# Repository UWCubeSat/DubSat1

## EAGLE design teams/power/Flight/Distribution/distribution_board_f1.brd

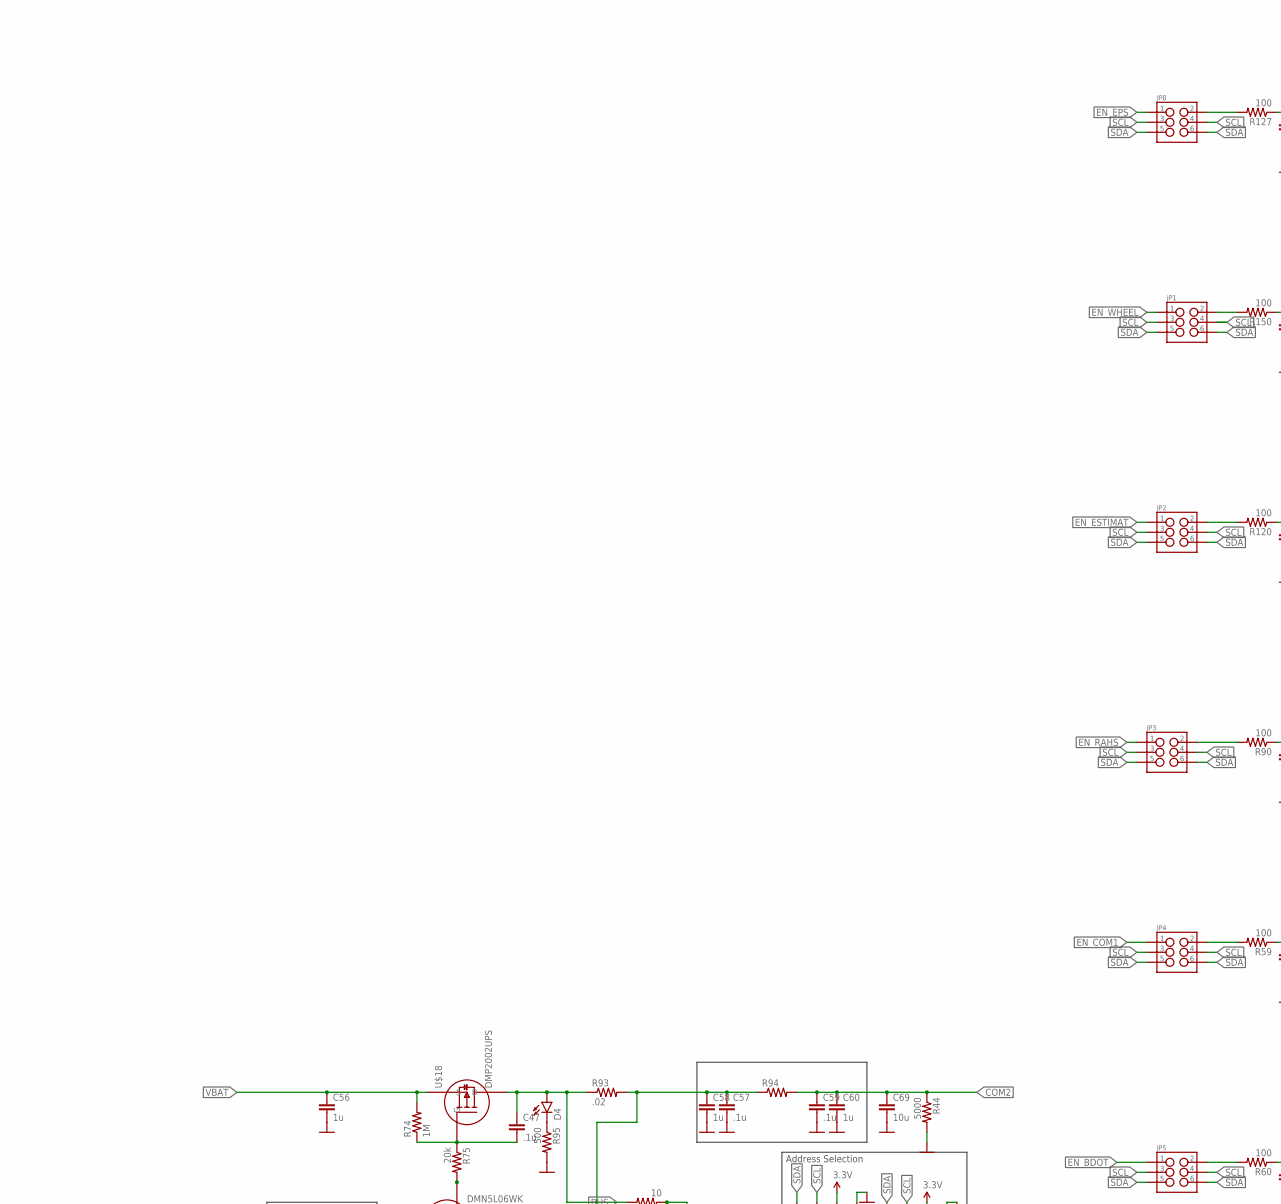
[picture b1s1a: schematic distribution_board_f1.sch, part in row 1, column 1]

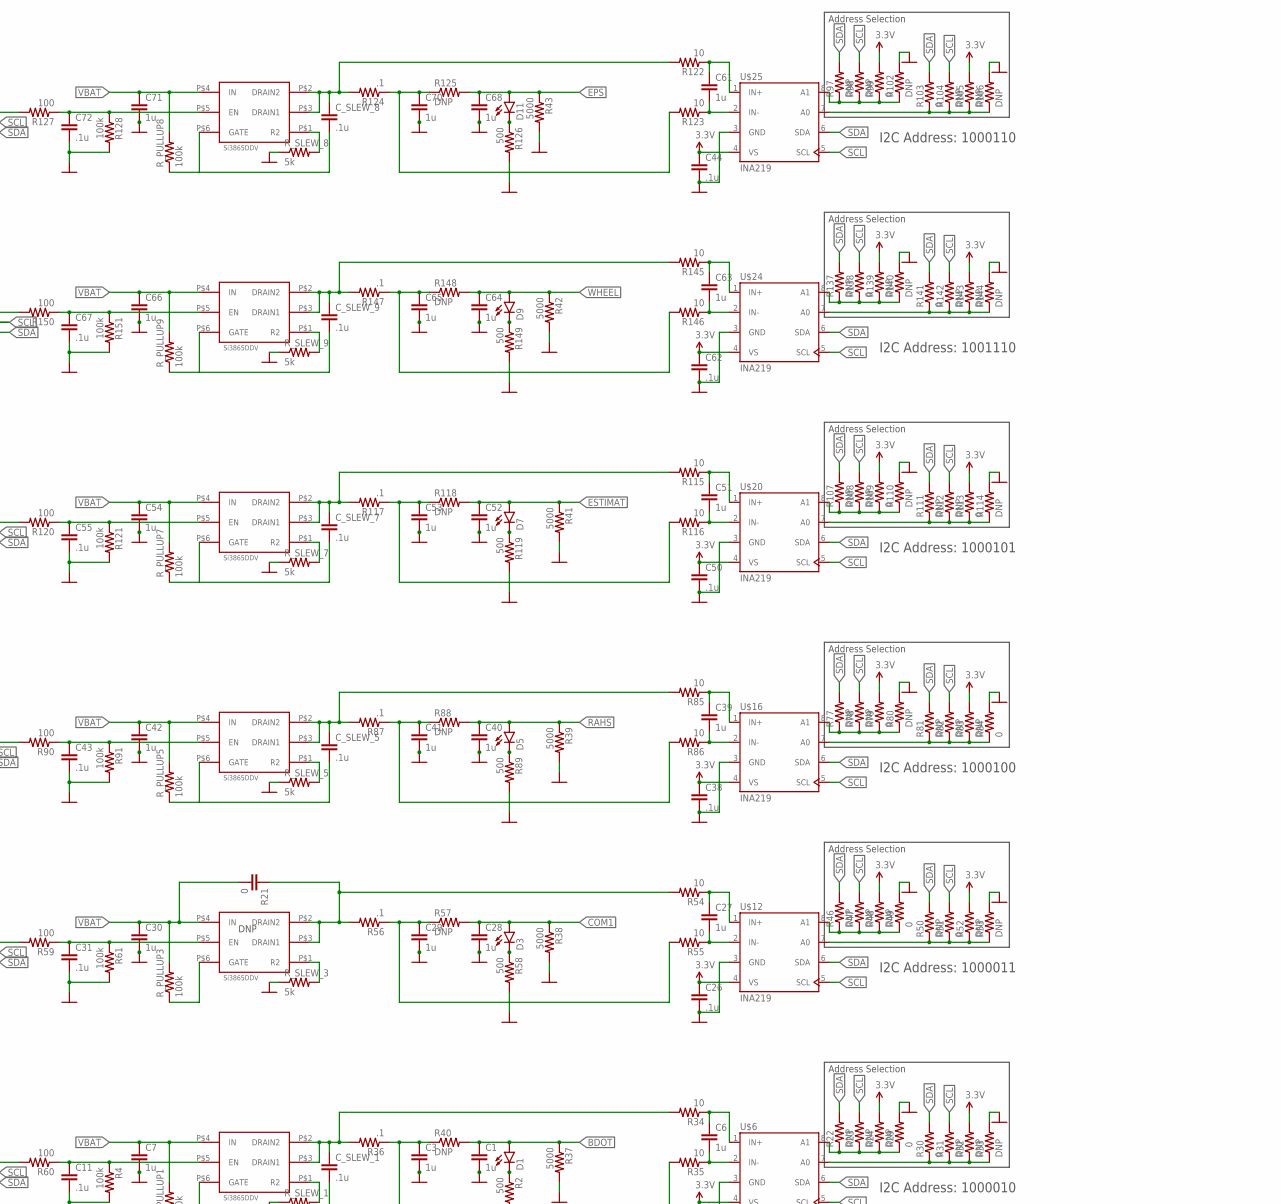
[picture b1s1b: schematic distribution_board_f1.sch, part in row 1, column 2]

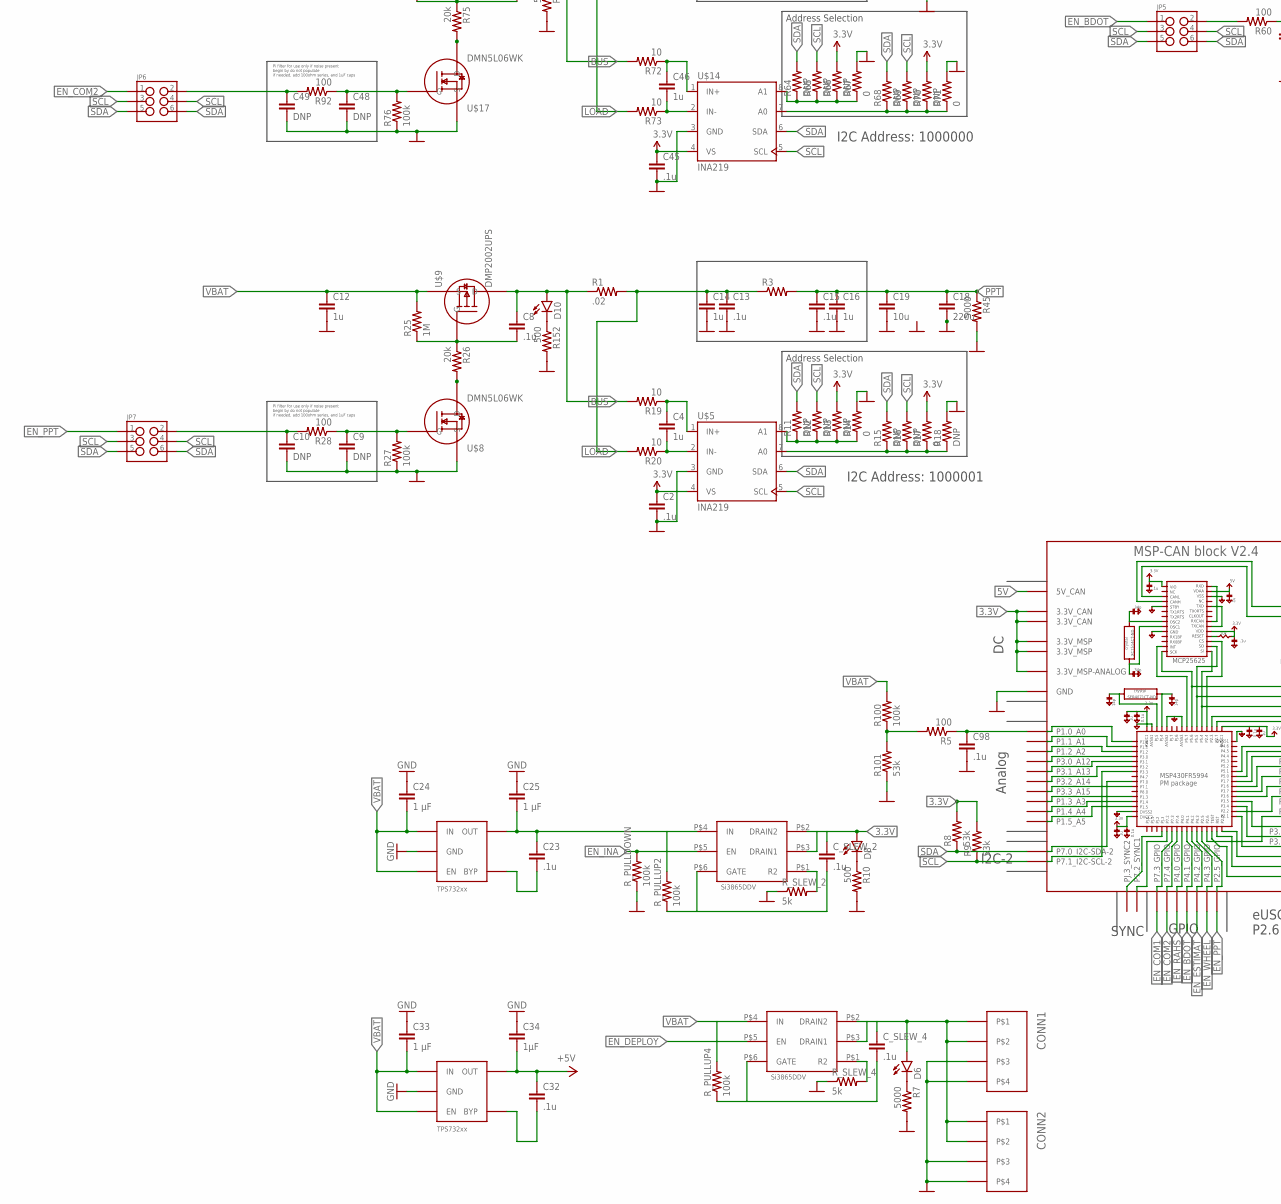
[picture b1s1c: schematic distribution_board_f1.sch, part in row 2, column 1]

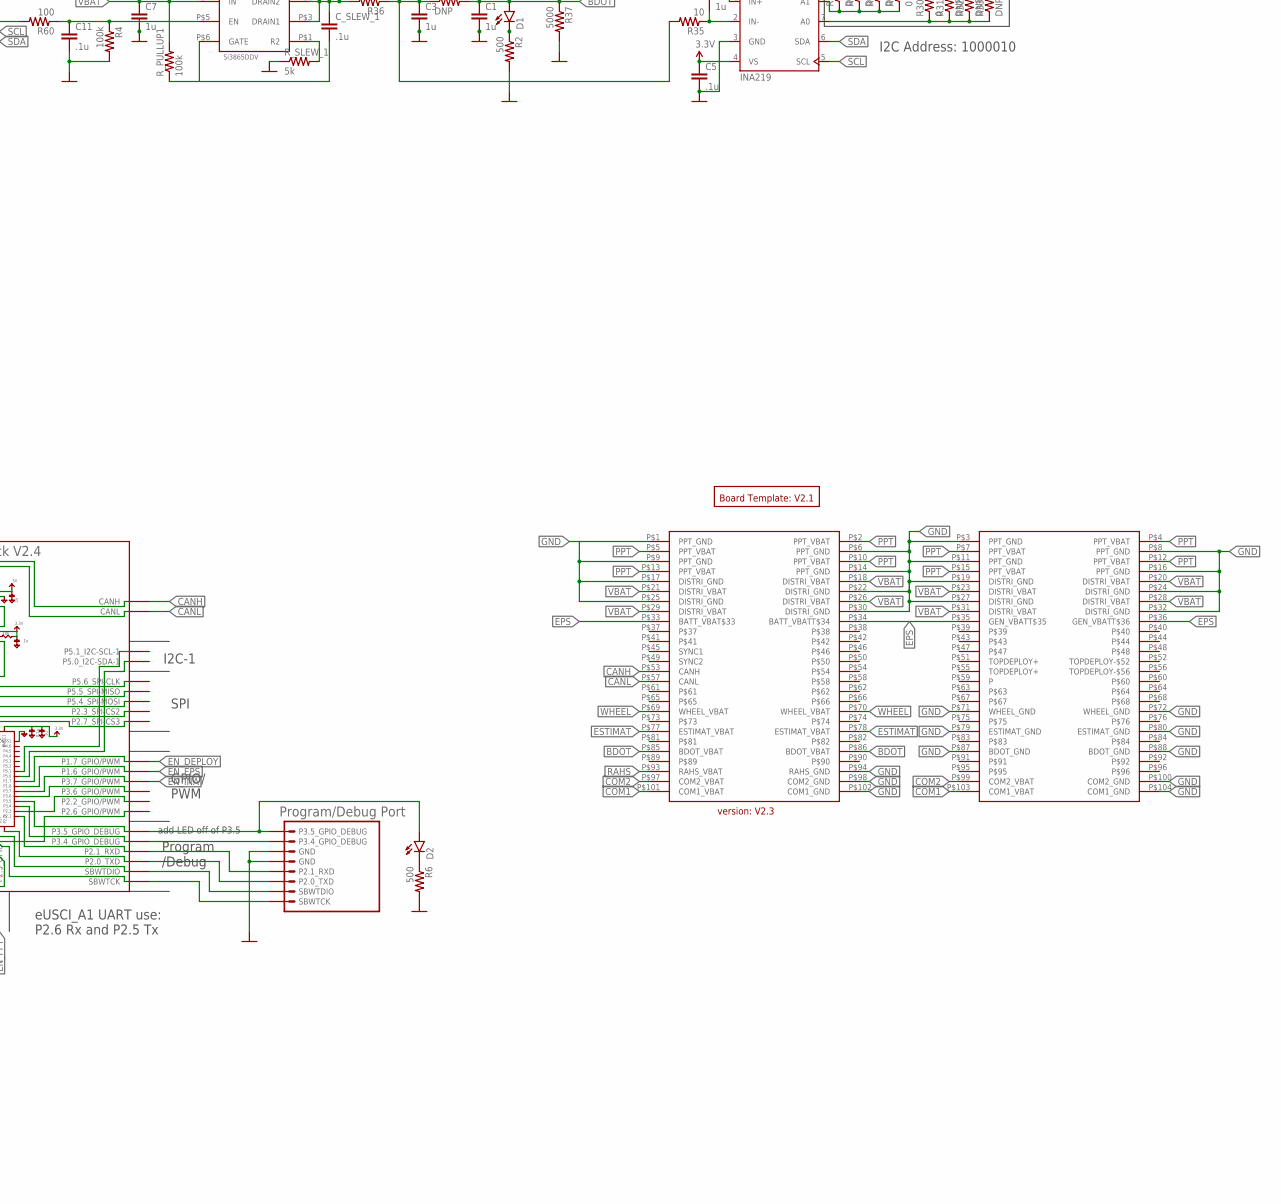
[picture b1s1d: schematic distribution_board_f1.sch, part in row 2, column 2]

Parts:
BLK1: MSP-CAN_BLOCK
C1, C3, C4, C6, C7, C12, C14, C16, C27, C28, C29, C30, C39, C40, C41, C42, C46, C51, C52, C53, C54, C56, C58, C60, C61, C63, C64, C65, C66, C68, C70, C71: 1u; 0805
C2, C5, C8, C11, C13, C15, C23, C26, C31, C32, C38, C43, C44, C45, C47, C50, C55, C57, C59, C62, C67, C72, C98: .1u; 0805
C9, C10, C48, C49: DNP; 0805
C18: 220u; 2917
C19, C69: 10u; 1210
C24, C25, C33: 1 μF; 0805
C34: 1μF; 0805
CONN1, CONN2: PICOLOCK_4-LEGACY
C_SLEW_1, C_SLEW_2, C_SLEW_4, C_SLEW_5, C_SLEW_7, C_SLEW_8, C_SLEW_9: .1u; 0805
D1, D2, D3, D4, D5, D6, D7, D8, D9, D10, D11: LED; LED-1206
JP1, JP2, JP3, JP4, JP5, JP6, JP7, JP8: M03X2NO_SILK; 2X3-NS
R1, R93: .02; R2010
R2, R6, R10, R58, R89, R95, R119, R126, R149, R152: 500; 0805
R3, R94: RESISTOR1206; 1206
R4, R27, R61, R76, R91, R100, R121, R128, R151: 100k; 0805
R5, R28, R59, R60, R90, R92, R120, R127, R150: 100; 0805
R7, R37, R38, R39, R41, R42, R43, R44, R45: 5000; 0805
R8, R9, R101: 53k; 0805
R11, R12, R13, R15, R16, R18, R22, R23, R24, R31, R32, R33, R40, R46, R47, R48, R50, R52, R53, R57, R64, R65, R66, R68, R69, R70, R77, R78, R80, R81, R82, R83, R88, R97, R98, R102, R104, R105, R106, R107, R108, R110, R111, R112, R114, R118, R125, R137, R139, R140, R142, R143, R144, R148: DNP; 0805
R14, R17, R21, R29, R30, R49, R51, R67, R71, R79, R84, R99, R103, R109, R113, R138, R141: 0; 0805
R19, R20, R34, R35, R54, R55, R72, R73, R85, R86, R115, R116, R122, R123, R145, R146: 10; 0805
R25, R74: 1M; 0805
R26, R75: 20k; 0805
R36, R56, R87, R117, R124, R147: .1; R2010
R_PULLDOWN: 100k; 0805
R_PULLUP1, R_PULLUP2, R_PULLUP3, R_PULLUP4, R_PULLUP5, R_PULLUP7, R_PULLUP8, R_PULLUP9: 100k; 0805
R_SLEW_1, R_SLEW_2, R_SLEW_3, R_SLEW_4, R_SLEW_5, R_SLEW_7, R_SLEW_8, R_SLEW_9: 5k; 0805
U2, U3: TPS732XX; SOT-23-5
U$1: PROGRAM/DEBUG_PORT; 1X08_CONNECTOR
U$2: PC104_CONNECTOR
U$3: BOARD_TEMPLATE1; BOARD_TEMPLATE
U$5, U$6, U$12, U$14, U$16, U$20, U$24, U$25: INA219; SOT-23-8
U$7, U$10, U$11, U$13, U$15, U$19, U$22, U$23: SI3865DDV; TSOP-6
U$8, U$17: DMN5L06WK; SOT-323
U$9, U$18: DMP2002UPS; POWERDI5060-8

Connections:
3.3V: BLK1.3.3V@CAN1 (3.3V_CAN), BLK1.3.3V@CAN2 (3.3V_CAN), BLK1.3.3V@MSP1 (3.3V_MSP), BLK1.3.3V@MSP2 (3.3V_MSP), BLK1.3.3V_ANALOG@MSP2 (3.3V_MSP-ANALOG), C2.1, C5.1, C23.1, C25.2, C26.1, C38.1, C44.1, C45.1, C50.1, C62.1, C_SLEW_2.1, D8.A, R8.2, R9.2, R13.2, R17.2, R24.2, R32.2, R48.2, R52.2, R66.2, R70.2, R79.2, R83.2, R99.2, R105.2, R109.2, R113.2, R139.2, R143.2, R_PULLUP2.2, U2.P$5 (OUT), U$5.4 (VS), U$6.4 (VS), U$7.P$2 (DRAIN2), U$7.P$3 (DRAIN1), U$7.P$4 (IN), U$12.4 (VS), U$14.4 (VS), U$16.4 (VS), U$20.4 (VS), U$24.4 (VS), U$25.4 (VS)
5V: BLK1.5V (5V_CAN), C32.1, C34.2, U3.P$5 (OUT)
BDOT: C1.1, D1.A, R37.1, R40.2, U$2.P$85 (BDOT_VBAT), U$2.P$86 (BDOT_VBAT)
BUS: C8.1, C47.1, D4.A, D10.A, R1.1, R19.2, R72.2, R93.1, U$9.D1 (D), U$9.D2 (D), U$9.D3 (D), U$9.D4 (D), U$9.D5 (D), U$18.D1 (D), U$18.D2 (D), U$18.D3 (D), U$18.D4 (D), U$18.D5 (D)
CANH: BLK1.CANH, U$2.P$53 (CANH)
CANL: BLK1.CANL, U$2.P$57 (CANL)
COM1: C28.1, D3.A, R38.1, R57.2, U$2.P$101 (COM1_VBAT), U$2.P$103 (COM1_VBAT)
COM2: C59.1, C60.1, C69.1, R44.1, R94.2, U$2.P$97 (COM2_VBAT), U$2.P$99 (COM2_VBAT)
DEPLOY: CONN1.P$1, CONN1.P$2, CONN2.P$1, CONN2.P$2, C_SLEW_4.1, D6.A, U$13.P$2 (DRAIN2), U$13.P$3 (DRAIN1)
EN_BDOT: BLK1.P4.1_GPIO, JP5.1, JP5.2, R60.2
EN_COM1: BLK1.P7.3_GPIO, JP4.1, JP4.2, R59.2
EN_COM2: BLK1.P7.4_GPIO, C49.1, JP6.1, JP6.2, R92.2
EN_DEPLOY: BLK1.P1.7_GPIO/PWM, U$13.P$5 (EN)
EN_EPS: BLK1.P1.6_GPIO/PWM, JP8.1, JP8.2, R127.2
EN_ESTIMAT: BLK1.P4.2_GPIO, JP2.1, JP2.2, R120.2
EN_INA: BLK1.P3.7_GPIO/PWM, R_PULLDOWN.2, U$7.P$5 (EN)
EN_PPT: BLK1.P2.5_GPIO, C10.1, JP7.1, JP7.2, R28.2
EN_RAHS: BLK1.P4.0_GPIO, JP3.1, JP3.2, R90.2
EN_WHEEL: BLK1.P4.3_GPIO, JP1.1, JP1.2, R150.2
EPS: C68.1, D11.A, R43.1, R125.2, U$2.P$33 (BATT_VBAT$33), U$2.P$34 (BATT_VBATT$34), U$2.P$35 (GEN_VBATT$35), U$2.P$36 (GEN_VBATT$36)
ESTIMAT: C52.1, D7.A, R41.1, R118.2, U$2.P$77 (ESTIMAT_VBAT), U$2.P$78 (ESTIMAT_VBAT)
GND: BLK1.GND@1 (GND), BLK1.GND@2 (GND), BLK1.GND@3 (GND), BLK1.GND@4 (GND), BLK1.GND@5 (GND), BLK1.GND@7 (GND), BLK1.GND@8 (GND), BLK1.GND@9 (GND), BLK1.GND@10 (GND), BLK1.GND@11 (GND), BLK1.GND@12 (GND), BLK1.GND@13 (GND), BLK1.GND@14 (GND), BLK1.GND@15 (GND), BLK1.GND@16 (GND), BLK1.GND@17 (GND), BLK1.GND@26 (GND), C1.2, C2.2, C3.2, C5.2, C7.2, C9.2, C10.2, C11.2, C12.2, C13.2, C14.2, C15.2, C16.2, C18.2, C19.2, C24.1, C25.1, C26.2, C28.2, C29.2, C30.2, C31.2, C33.1, C34.1, C38.2, C40.2, C41.2, C42.2, C43.2, C44.2, C45.2, C48.2, C49.2, C50.2, C52.2, C53.2, C54.2, C55.2, C56.2, C57.2, C58.2, C59.2, C60.2, C62.2, C64.2, C65.2, C66.2, C67.2, C68.2, C69.2, C70.2, C71.2, C72.2, C98.2, CONN1.P$3, CONN1.P$4, CONN2.P$3, CONN2.P$4, R2.2, R4.2, R6.2, R7.2, R10.2, R14.2, R18.2, R27.1, R29.2, R33.2, R37.2, R38.2, R39.2, R41.2, R42.2, R43.2, R44.2, R45.2, R49.2, R53.2, R58.2, R61.2, R67.2, R71.2, R76.1, R80.2, R84.2, R89.2, R91.2, R95.2, R101.1, R102.2, R106.2, R110.2, R114.2, R119.2, R121.2, R126.2, R128.2, R140.2, R144.2, R149.2, R151.2, R152.2, R_PULLDOWN.1, R_SLEW_1.1, R_SLEW_2.1, R_SLEW_3.1, R_SLEW_4.1, R_SLEW_5.1, R_SLEW_7.1, R_SLEW_8.1, R_SLEW_9.1, U2.P$2 (GND), U3.P$2 (GND), U$1.5 (GND), U$1.6 (GND), U$2.P$1 (PPT_GND), U$2.P$3 (PPT_GND), U$2.P$6 (PPT_GND), U$2.P$8 (PPT_GND), U$2.P$9 (PPT_GND), U$2.P$11 (PPT_GND), U$2.P$14 (PPT_GND), U$2.P$16 (PPT_GND), U$2.P$17 (DISTRI_GND), U$2.P$19 (DISTRI_GND), U$2.P$22 (DISTRI_GND), U$2.P$24 (DISTRI_GND), U$2.P$27 (DISTRI_GND), U$2.P$30 (DISTRI_GND), U$2.P$32 (DISTRI_GND), U$2.P$71 (WHEEL_GND), U$2.P$72 (WHEEL_GND), U$2.P$79 (ESTIMAT_GND), U$2.P$80 (ESTIMAT_GND), U$2.P$87 (BDOT_GND), U$2.P$88 (BDOT_GND), U$2.P$94 (RAHS_GND), U$2.P$98 (COM2_GND), U$2.P$100 (COM2_GND), U$2.P$102 (COM1_GND), U$2.P$104 (COM1_GND), U$5.3 (GND), U$6.3 (GND), U$8.2 (S), U$12.3 (GND), U$14.3 (GND), U$16.3 (GND), U$17.2 (S), U$20.3 (GND), U$24.3 (GND), U$25.3 (GND)
INA219_A0_1: R15.1, R16.1, R17.1, R18.1, U$5.7 (A0)
INA219_A0_2: R30.1, R31.1, R32.1, R33.1, U$6.7 (A0)
INA219_A0_4: R50.1, R51.1, R52.1, R53.1, U$12.7 (A0)
INA219_A0_5: R68.1, R69.1, R70.1, R71.1, U$14.7 (A0)
INA219_A0_6: R81.1, R82.1, R83.1, R84.1, U$16.7 (A0)
INA219_A0_7: R103.1, R104.1, R105.1, R106.1, U$25.7 (A0)
INA219_A0_8: R111.1, R112.1, R113.1, R114.1, U$20.7 (A0)
INA219_A0_10: R141.1, R142.1, R143.1, R144.1, U$24.7 (A0)
INA219_A1_1: R11.1, R12.1, R13.1, R14.1, U$5.8 (A1)
INA219_A1_2: R22.1, R23.1, R24.1, R29.1, U$6.8 (A1)
INA219_A1_4: R46.1, R47.1, R48.1, R49.1, U$12.8 (A1)
INA219_A1_5: R64.1, R65.1, R66.1, R67.1, U$14.8 (A1)
INA219_A1_6: R77.1, R78.1, R79.1, R80.1, U$16.8 (A1)
INA219_A1_7: R97.1, R98.1, R99.1, R102.1, U$25.8 (A1)
INA219_A1_8: R107.1, R108.1, R109.1, R110.1, U$20.8 (A1)
INA219_A1_10: R137.1, R138.1, R139.1, R140.1, U$24.8 (A1)
INA219_IN+_1: C4.1, R19.1, U$5.1 (IN+)
INA219_IN+_2: C6.1, R34.1, U$6.1 (IN+)
INA219_IN+_4: C27.1, R54.1, U$12.1 (IN+)
INA219_IN+_5: C46.1, R72.1, U$14.1 (IN+)
INA219_IN+_6: C39.1, R85.1, U$16.1 (IN+)
INA219_IN+_7: C61.1, R122.1, U$25.1 (IN+)
INA219_IN+_8: C51.1, R115.1, U$20.1 (IN+)
INA219_IN+_10: C63.1, R145.1, U$24.1 (IN+)
INA219_IN-_1: C4.2, R20.1, U$5.2 (IN-)
INA219_IN-_2: C6.2, R35.1, U$6.2 (IN-)
INA219_IN-_4: C27.2, R55.1, U$12.2 (IN-)
INA219_IN-_5: C46.2, R73.1, U$14.2 (IN-)
INA219_IN-_6: C39.2, R86.1, U$16.2 (IN-)
INA219_IN-_7: C61.2, R123.1, U$25.2 (IN-)
INA219_IN-_8: C51.2, R116.1, U$20.2 (IN-)
INA219_IN-_10: C63.2, R146.1, U$24.2 (IN-)
LDO_3V3_BYP2: C23.2, U2.P$4 (BYP)
LDO_5V_BYP2: C32.2, U3.P$4 (BYP)
LOAD: C13.1, C14.1, C57.1, C58.1, R1.2, R3.1, R20.2, R73.2, R93.2, R94.1
unnamed: C8.2, R25.1, R26.1, U$9.G
unnamed: C9.1, R27.2, R28.1, U$8.1 (G)
unnamed: D1.C, R2.1
unnamed: C11.1, R4.1, R60.1, U$11.P$5 (EN)
unnamed: R5.2, R100.1, R101.2
unnamed: R26.2, U$8.3 (D)
unnamed: BLK1.P1.0_A0, C98.1, R5.1
unnamed: R_SLEW_2.2, U$7.P$1 (R2)
unnamed: R_SLEW_1.2, U$11.P$1 (R2)
unnamed: C_SLEW_1.2, R_PULLUP1.1, U$11.P$6 (GATE)
unnamed: C_SLEW_2.2, R_PULLUP2.1, U$7.P$6 (GATE)
unnamed: R_SLEW_3.2, U$10.P$1 (R2)
unnamed: R_PULLUP3.1, U$10.P$6 (GATE)
unnamed: D3.C, R58.1
unnamed: C31.1, R59.1, R61.1, U$10.P$5 (EN)
unnamed: C47.2, R74.1, R75.1, U$18.G
unnamed: C48.1, R76.2, R92.1, U$17.1 (G)
unnamed: R75.2, U$17.3 (D)
unnamed: D4.C, R95.1
unnamed: R_SLEW_5.2, U$15.P$1 (R2)
unnamed: C_SLEW_5.2, R_PULLUP5.1, U$15.P$6 (GATE)
unnamed: D5.C, R89.1
unnamed: C43.1, R90.1, R91.1, U$15.P$5 (EN)
unnamed: BLK1.P3.5_GPIO_DEBUG, D2.A, U$1.8 (P3.5_GPIO_DEBUG)
unnamed: BLK1.P3.4_GPIO_DEBUG, U$1.7 (P3.4_GPIO_DEBUG)
unnamed: BLK1.P2.1_RXD, U$1.4 (P2.1_RXD)
unnamed: BLK1.P2.0_TXD, U$1.3 (P2.0_TXD)
unnamed: R_SLEW_7.2, U$19.P$1 (R2)
unnamed: C_SLEW_7.2, R_PULLUP7.1, U$19.P$6 (GATE)
unnamed: D7.C, R119.1
unnamed: C55.1, R120.1, R121.1, U$19.P$5 (EN)
unnamed: BLK1.SBWTDIO, U$1.2 (SBWTDIO)
unnamed: BLK1.SBWTCK, U$1.SBWTCK
unnamed: R_SLEW_4.2, U$13.P$1 (R2)
unnamed: C_SLEW_4.2, R_PULLUP4.1, U$13.P$6 (GATE)
unnamed: R_SLEW_9.2, U$23.P$1 (R2)
unnamed: C_SLEW_9.2, R_PULLUP9.1, U$23.P$6 (GATE)
unnamed: D9.C, R149.1
unnamed: C67.1, R150.1, R151.1, U$23.P$5 (EN)
unnamed: D10.C, R152.1
unnamed: D2.C, R6.1
unnamed: D8.C, R10.1
unnamed: D6.C, R7.1
unnamed: R_SLEW_8.2, U$22.P$1 (R2)
unnamed: C_SLEW_8.2, R_PULLUP8.1, U$22.P$6 (GATE)
unnamed: D11.C, R126.1
unnamed: C72.1, R127.1, R128.1, U$22.P$5 (EN)
OUTPUT1: C3.1, R35.2, R36.1, R40.1
OUTPUT3: C29.1, R55.2, R56.1, R57.1
OUTPUT4: C70.1, R123.2, R124.1, R125.1
OUTPUT5: C41.1, R86.2, R87.1, R88.1
OUTPUT7: C53.1, R116.2, R117.1, R118.1
OUTPUT9: C65.1, R146.2, R147.1, R148.1
OUT_1: C_SLEW_1.1, R34.2, R36.2, U$11.P$2 (DRAIN2), U$11.P$3 (DRAIN1)
OUT_3: R21.1, R54.2, R56.2, U$10.P$2 (DRAIN2), U$10.P$3 (DRAIN1)
OUT_4: C_SLEW_8.1, R122.2, R124.2, U$22.P$2 (DRAIN2), U$22.P$3 (DRAIN1)
OUT_5: C_SLEW_5.1, R85.2, R87.2, U$15.P$2 (DRAIN2), U$15.P$3 (DRAIN1)
OUT_7: C_SLEW_7.1, R115.2, R117.2, U$19.P$2 (DRAIN2), U$19.P$3 (DRAIN1)
OUT_9: C_SLEW_9.1, R145.2, R147.2, U$23.P$2 (DRAIN2), U$23.P$3 (DRAIN1)
PPT: C15.1, C16.1, C18.1, C19.1, R3.2, R45.1, U$2.P$2 (PPT_VBAT), U$2.P$4 (PPT_VBAT), U$2.P$5 (PPT_VBAT), U$2.P$7 (PPT_VBAT), U$2.P$10 (PPT_VBAT), U$2.P$12 (PPT_VBAT), U$2.P$13 (PPT_VBAT), U$2.P$15 (PPT_VBAT)
RAHS: C40.1, D5.A, R39.1, R88.2, U$2.P$93 (RAHS_VBAT)
SCL: BLK1.P7.1_I2C-SCL-2, JP1.3, JP1.4, JP2.3, JP2.4, JP3.3, JP3.4, JP4.3, JP4.4, JP5.3, JP5.4, JP6.3, JP6.4, JP7.3, JP7.4, JP8.3, JP8.4, R9.1, R12.2, R16.2, R23.2, R31.2, R47.2, R51.2, R65.2, R69.2, R78.2, R82.2, R98.2, R104.2, R108.2, R112.2, R138.2, R142.2, U$5.5 (SCL), U$6.5 (SCL), U$12.5 (SCL), U$14.5 (SCL), U$16.5 (SCL), U$20.5 (SCL), U$24.5 (SCL), U$25.5 (SCL)
SDA: BLK1.P7.0_I2C-SDA-2, JP1.5, JP1.6, JP2.5, JP2.6, JP3.5, JP3.6, JP4.5, JP4.6, JP5.5, JP5.6, JP6.5, JP6.6, JP7.5, JP7.6, JP8.5, JP8.6, R8.1, R11.2, R15.2, R22.2, R30.2, R46.2, R50.2, R64.2, R68.2, R77.2, R81.2, R97.2, R103.2, R107.2, R111.2, R137.2, R141.2, U$5.6 (SDA), U$6.6 (SDA), U$12.6 (SDA), U$14.6 (SDA), U$16.6 (SDA), U$20.6 (SDA), U$24.6 (SDA), U$25.6 (SDA)
VBAT: C7.1, C12.1, C24.2, C30.1, C33.2, C42.1, C54.1, C56.1, C66.1, C71.1, R21.2, R25.2, R74.2, R100.2, R_PULLUP1.2, R_PULLUP3.2, R_PULLUP4.2, R_PULLUP5.2, R_PULLUP7.2, R_PULLUP8.2, R_PULLUP9.2, U2.P$1 (IN), U2.P$3 (EN), U3.P$1 (IN), U3.P$3 (EN), U$2.P$18 (DISTRI_VBAT), U$2.P$20 (DISTRI_VBAT), U$2.P$21 (DISTRI_VBAT), U$2.P$23 (DISTRI_VBAT), U$2.P$26 (DISTRI_VBAT), U$2.P$28 (DISTRI_VBAT), U$2.P$29 (DISTRI_VBAT), U$2.P$31 (DISTRI_VBAT), U$9.S1 (S), U$9.S2 (S), U$9.S3 (S), U$10.P$4 (IN), U$11.P$4 (IN), U$13.P$4 (IN), U$15.P$4 (IN), U$18.S1 (S), U$18.S2 (S), U$18.S3 (S), U$19.P$4 (IN), U$22.P$4 (IN), U$23.P$4 (IN)
WHEEL: C64.1, D9.A, R42.1, R148.2, U$2.P$69 (WHEEL_VBAT), U$2.P$70 (WHEEL_VBAT)

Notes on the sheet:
Address Selection
Pi filter for use only if noise present begin by do not populate if needed, add 100ohm series, and 1uF caps
I2C Address: 1000000
I2C Address: 1000001
I2C Address: 1000010
I2C Address: 1000011
I2C Address: 1000100
I2C Address: 1000101
I2C Address: 1001110
I2C Address: 1000110
DNP

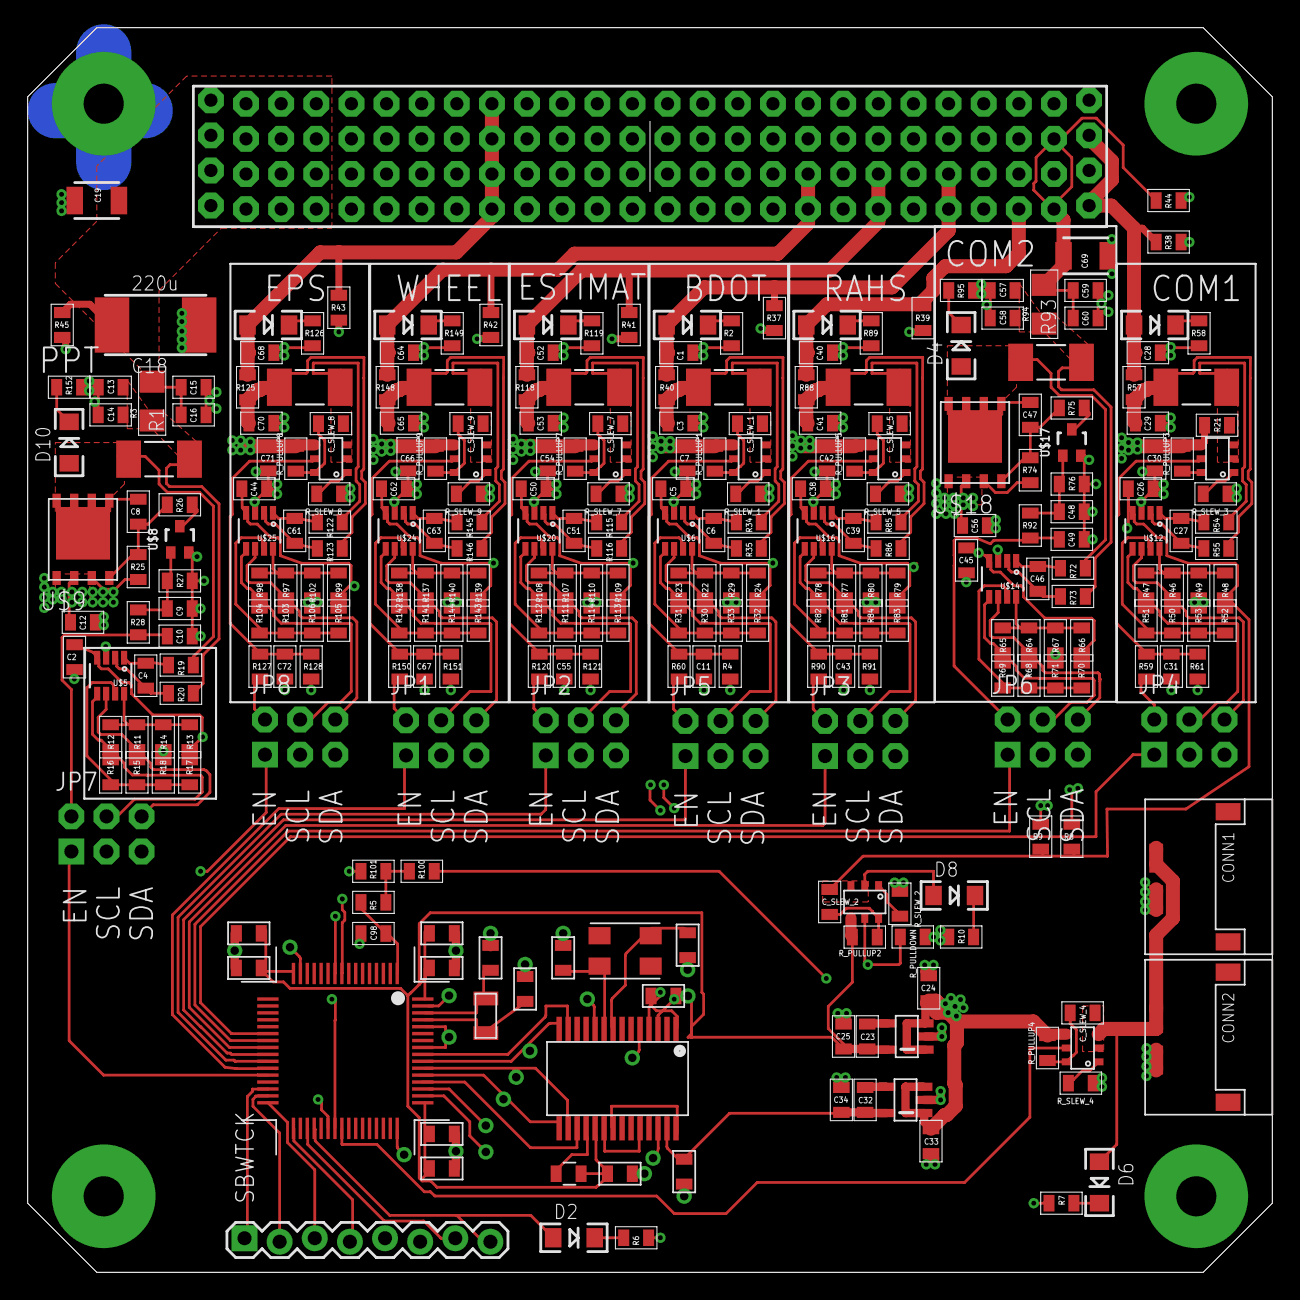
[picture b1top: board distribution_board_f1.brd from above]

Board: 4 copper layers, 90.0 x 90.0 mm, 278 parts (0 on the bottom side), 122 nets.

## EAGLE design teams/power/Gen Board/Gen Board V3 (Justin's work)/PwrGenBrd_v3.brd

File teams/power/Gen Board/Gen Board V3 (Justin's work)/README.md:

# This is an ordered bord, do not modify. See a newer version.

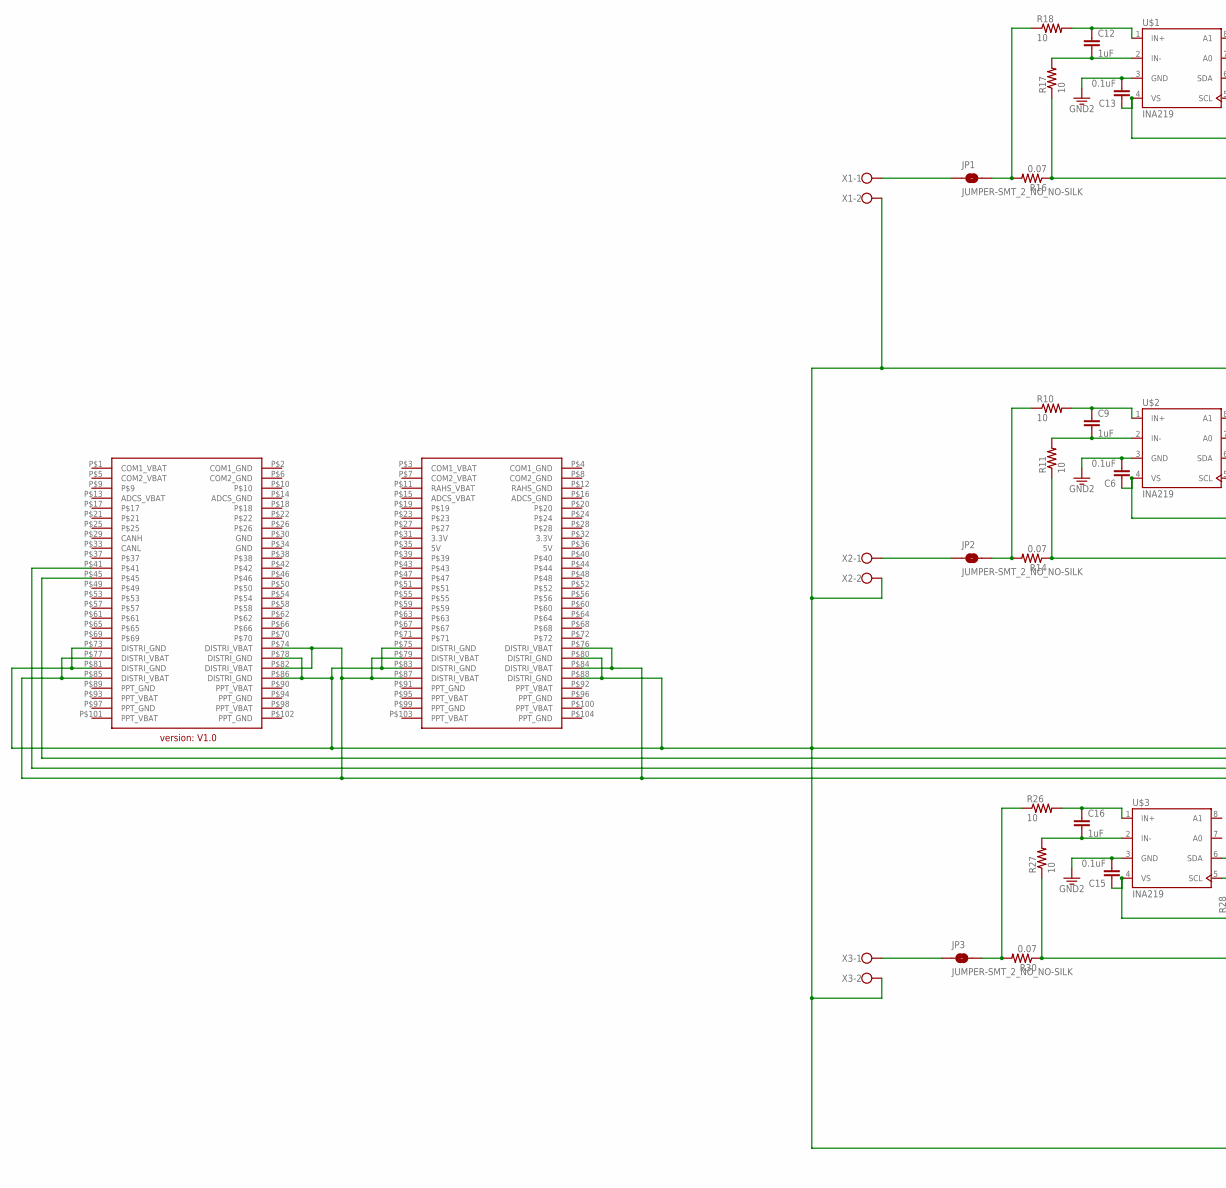
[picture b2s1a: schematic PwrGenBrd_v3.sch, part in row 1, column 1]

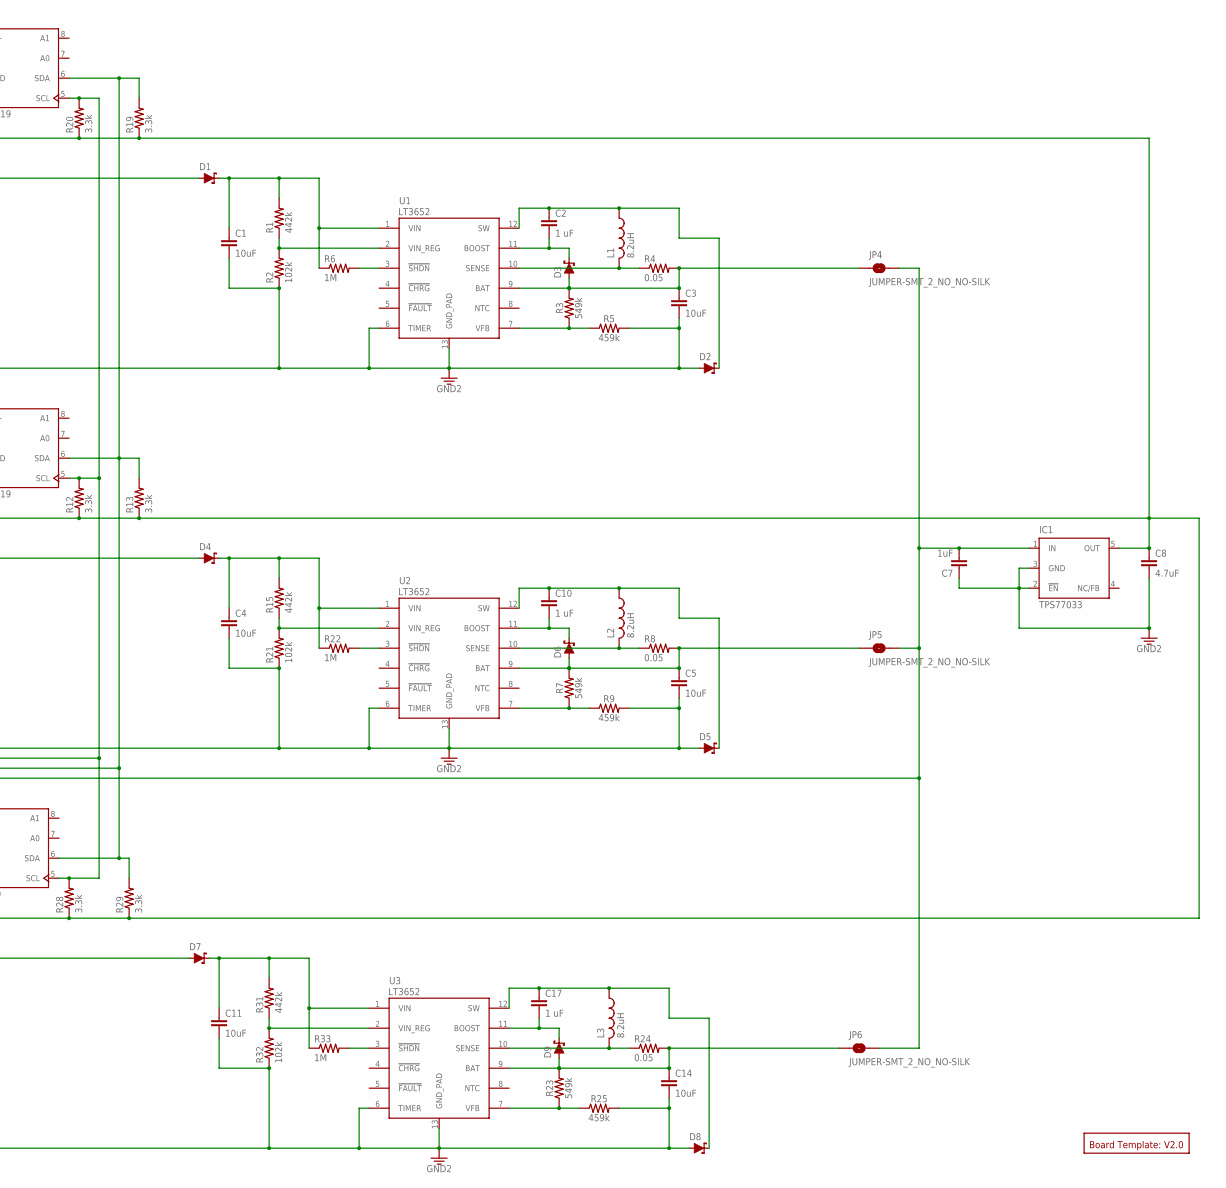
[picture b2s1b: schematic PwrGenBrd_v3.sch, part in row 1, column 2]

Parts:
C1, C3, C4, C5, C11, C14: 10uF; 1210
C2, C10, C17: 1 uF; C0805
C6, C13, C15: 0.1uF; C0201
C7, C9, C12, C16: 1uF; C1210
C8: 4.7uF; 0603
D1, D2, D4, D5, D7, D8: DIODE-SCHOTTKY-B340A; SMA-DIODE
D3, D6, D9: DIODE-SCHOTTKY-ZLLS500; SOT23-3
IC1: TPS77033; SOT23-DBV
JP1, JP2, JP3, JP4, JP5, JP6: JUMPER-SMT_2_NO_NO-SILK; SMT-JUMPER_2_NO_NO-SILK
L1, L2, L3: 8.2uH; L1812
R1, R15, R31: 442k; R0402
R2, R21, R32: 102k; R0402
R3, R7, R23: 549k; 0805
R4, R8, R24: 0.05; R2512
R5, R9, R25: 459k; 1206
R6, R22, R33: 1M; R0402
R10, R11, R17, R18, R26, R27: 10; R0402
R12, R13, R19, R20, R28, R29: 3.3k; R0603
R14, R16, R30: 0.07; R2512
U1, U2, U3: LT3652; MSOP-12_GND
U$1, U$2, U$3: INA219; SO08
U$4: 2X26_CONNECTOR; 4X26_CONNECTOR_(V1.0)
U$5: BOARD_TEMPLATE; BOARD_TEMPLATE_(V2.0)
X1, X2, X3: W237-102

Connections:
BATT: C3.1, D3.1 (A), JP4.1, R3.2, R4.2, U1.9 (BAT)
BATT1: C5.1, D6.1 (A), JP5.1, R7.2, R8.2, U2.9 (BAT)
BATT2: C14.1, D9.1 (A), JP6.1, R23.2, R24.2, U3.9 (BAT)
BOOST: C2.2, D3.3 (C), U1.11 (BOOST)
BOOST1: C10.2, D6.3 (C), U2.11 (BOOST)
BOOST2: C17.2, D9.3 (C), U3.11 (BOOST)
GND: C1.2, C3.2, C4.2, C5.2, C6.2, C11.2, C13.2, C14.2, C15.2, D2.A, D5.A, D8.A, R2.1, R5.2, R9.2, R21.1, R25.2, R32.1, U1.6 (TIMER), U1.13 (GND_PAD), U2.6 (TIMER), U2.13 (GND_PAD), U3.6 (TIMER), U3.13 (GND_PAD), U$1.3 (GND), U$2.3 (GND), U$3.3 (GND), U$4.P$73 (DISTRI_GND), U$4.P$75 (DISTRI_GND), U$4.P$78 (DISTRI_GND), U$4.P$80 (DISTRI_GND), U$4.P$81 (DISTRI_GND), U$4.P$83 (DISTRI_GND), U$4.P$86 (DISTRI_GND), U$4.P$88 (DISTRI_GND), X1.2, X2.2, X3.2
GND4: C7.1, C8.2, IC1.2 (!EN), IC1.3 (GND)
IN+: C12.1, R18.2, U$1.1 (IN+)
IN+1: C9.1, R10.2, U$2.1 (IN+)
IN+2: C16.1, R26.2, U$3.1 (IN+)
IN++: JP1.2, R16.2, R18.1
IN++1: JP2.2, R10.1, R14.2
IN++2: JP3.2, R26.1, R30.2
IN-: C12.2, R17.2, U$1.2 (IN-)
IN-1: C9.2, R11.2, U$2.2 (IN-)
IN-2: C16.2, R27.2, U$3.2 (IN-)
IN--: D1.A, R16.1, R17.1
IN--1: D4.A, R11.1, R14.1
IN--2: D7.A, R27.1, R30.1
unnamed: R6.2, U1.3 (!SHDN)
PNL1: JP1.1, X1.1
PNL2: JP2.1, X2.1
PNL3: JP3.1, X3.1
SCL: R12.2, R20.2, R28.2, U$1.5 (SCL), U$2.5 (SCL), U$3.5 (SCL), U$4.P$45
SDA: R13.2, R19.2, R29.2, U$1.6 (SDA), U$2.6 (SDA), U$3.6 (SDA), U$4.P$41
SENSE: L1.2, R4.1, U1.10 (SENSE)
SENSE1: L2.2, R8.1, U2.10 (SENSE)
SENSE2: L3.2, R24.1, U3.10 (SENSE)
SHDN2: R22.2, U2.3 (!SHDN)
SHDN3: R33.2, U3.3 (!SHDN)
SW: C2.1, D2.C, L1.1, U1.12 (SW)
SW1: C10.1, D5.C, L2.1, U2.12 (SW)
SW2: C17.1, D8.C, L3.1, U3.12 (SW)
VBATT: C7.2, IC1.1 (IN), JP4.2, JP5.2, JP6.2, U$4.P$74 (DISTRI_VBAT), U$4.P$76 (DISTRI_VBAT), U$4.P$77 (DISTRI_VBAT), U$4.P$79 (DISTRI_VBAT), U$4.P$82 (DISTRI_VBAT), U$4.P$84 (DISTRI_VBAT), U$4.P$85 (DISTRI_VBAT), U$4.P$87 (DISTRI_VBAT)
VFB: R3.1, R5.1, U1.7 (VFB)
VFB1: R7.1, R9.1, U2.7 (VFB)
VFB2: R23.1, R25.1, U3.7 (VFB)
VIN: C1.1, D1.C, R1.2, R6.1, U1.1 (VIN)
VIN1: C4.1, D4.C, R15.2, R22.1, U2.1 (VIN)
VIN2: C11.1, D7.C, R31.2, R33.1, U3.1 (VIN)
VIN_REG: R1.1, R2.2, U1.2 (VIN_REG)
VIN_REG1: R15.1, R21.2, U2.2 (VIN_REG)
VIN_REG2: R31.1, R32.2, U3.2 (VIN_REG)
VS: C6.1, C8.1, C13.1, C15.1, IC1.5 (OUT), R12.1, R13.1, R19.1, R20.1, R28.1, R29.1, U$1.4 (VS), U$2.4 (VS), U$3.4 (VS)

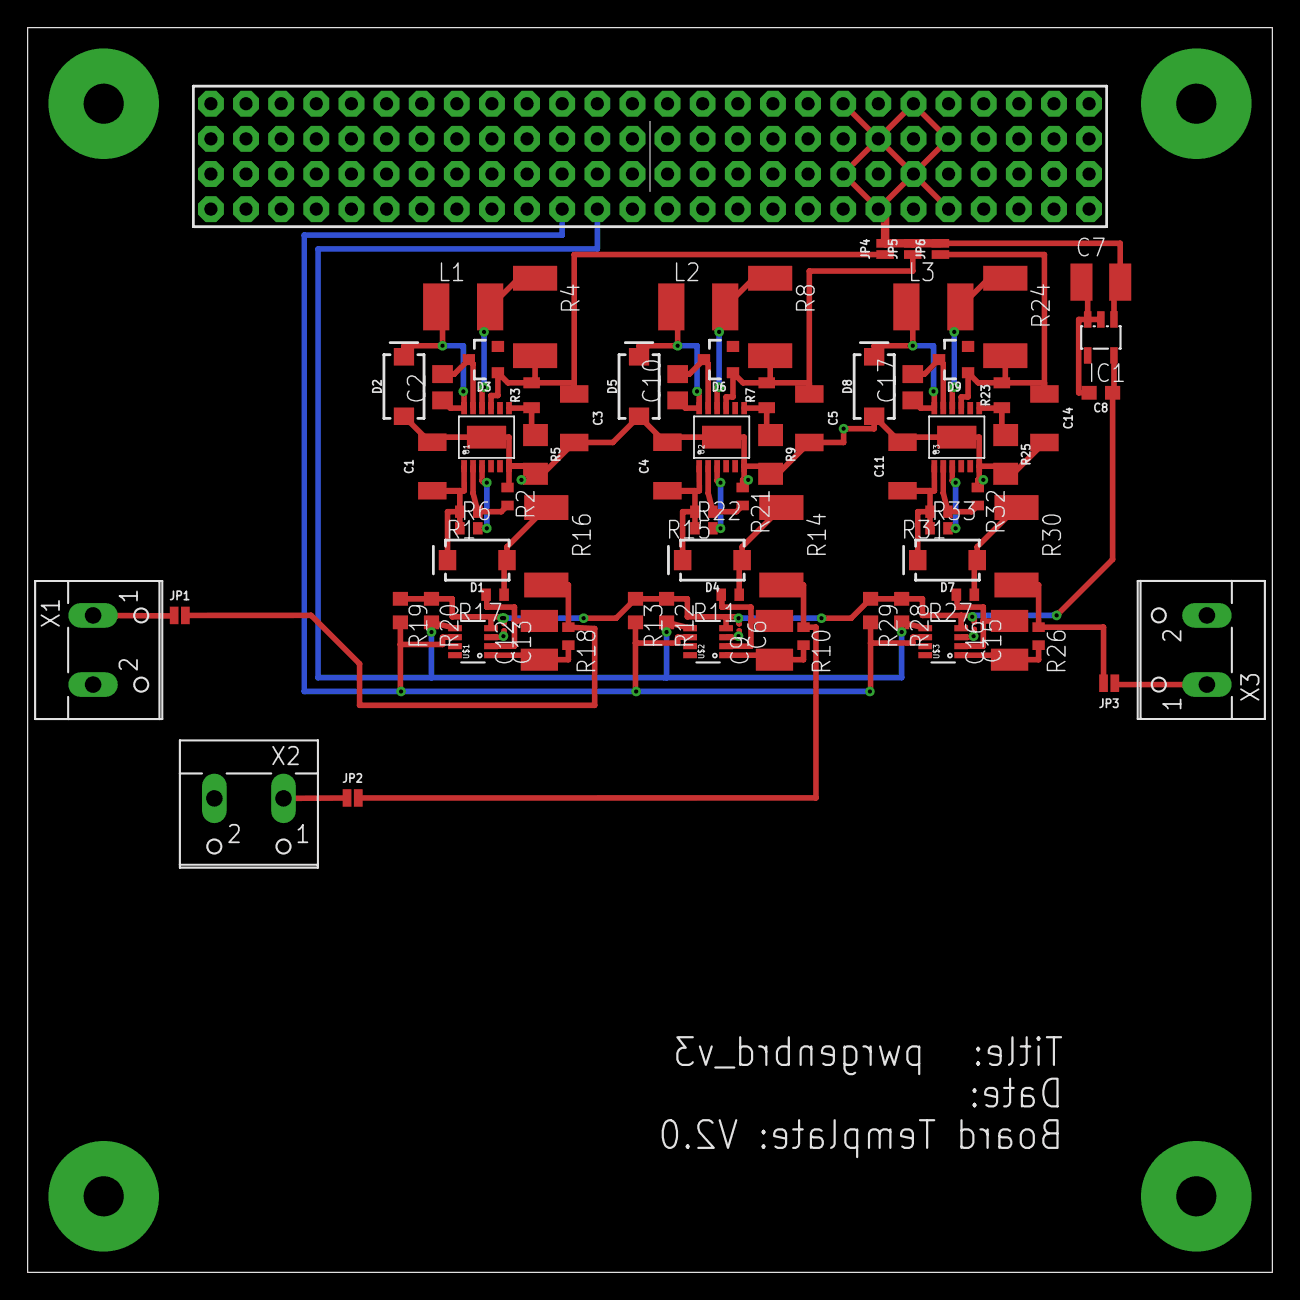
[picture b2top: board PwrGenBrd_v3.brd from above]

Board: 4 copper layers, 90.0 x 90.0 mm, 80 parts (0 on the bottom side), 45 nets.

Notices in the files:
parts and their libraries:
SparkFun-Connectors: Licensing: Creative Commons ShareAlike 4.0 International - https://creativecommons.org/licenses/by-sa/4.0
